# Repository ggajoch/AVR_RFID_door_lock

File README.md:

# AVR_RFID_door_lock
Door lock and opener using AVR microcontroller and RFID card

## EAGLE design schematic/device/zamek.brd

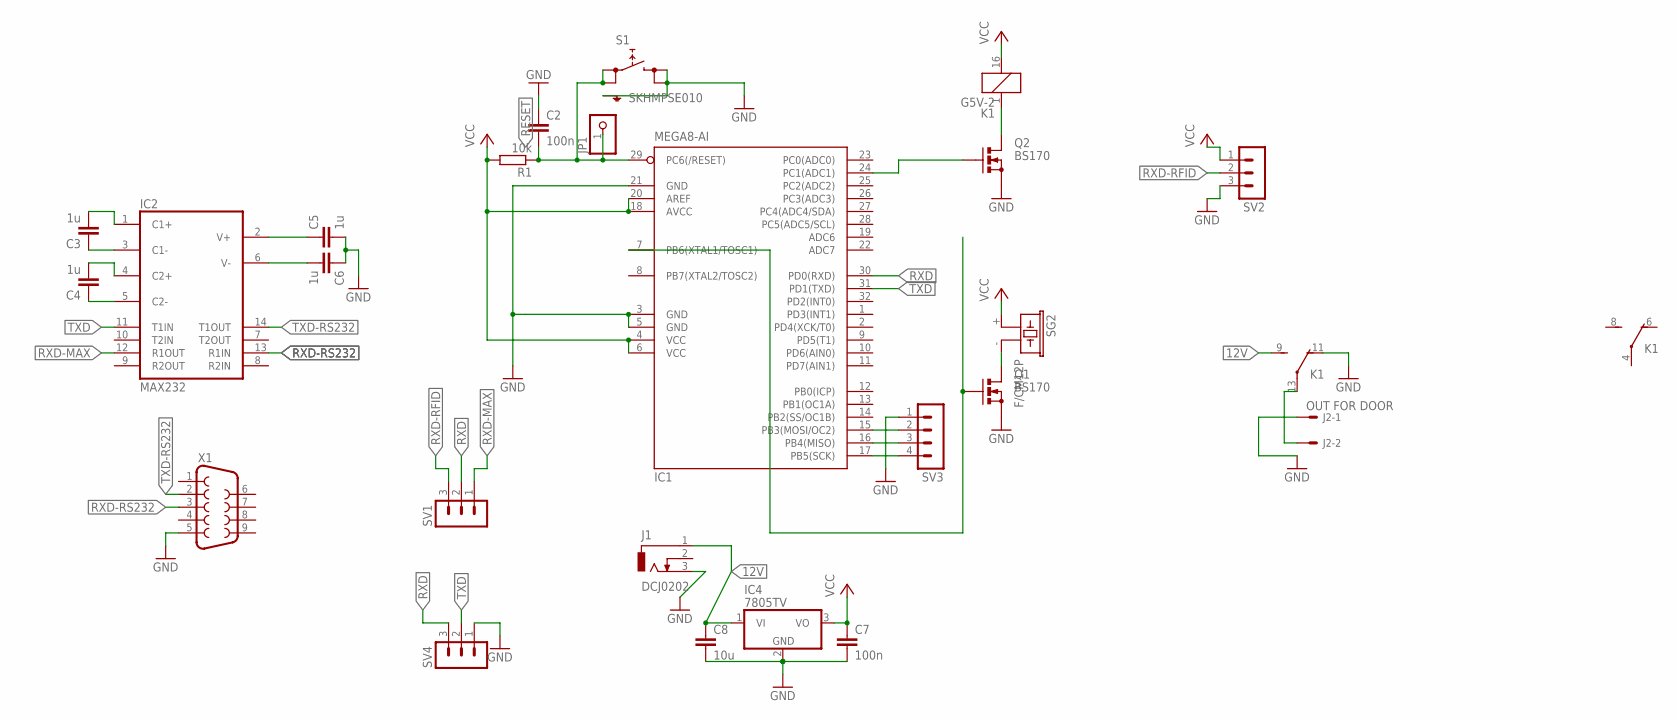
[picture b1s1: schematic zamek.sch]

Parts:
C2, C7: 100n; C1206
C3, C4, C5, C6: 1u; C1206
C8: 10u; C5B3
IC1: MEGA8-AI; TQFP32-08
IC2: MAX232; DIL16
IC4: 7805TV; TO220V
J1: DCJ0202
J2: OUT FOR DOOR; 6410-02
JP1: PINHD-1X1; 1X01
K1: G5V-2
Q1, Q2: BS170; SOT54E
R1: 10k; R1206
S1: SKHMPSE010; SKHMPXE010
SG2: F/CM12P
SV1, SV2, SV4: MA03-1
SV3: MA04-1
X1: F09HP

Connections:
12V: C8.1, IC4.1 (VI), J1.1, K1.9 (S)
GND: C2.1, C5.2, C6.1, C7.2, C8.2, IC1.3 (GND), IC1.5 (GND), IC1.21 (GND), IC2.15 (GND), IC4.2 (GND), J1.3, J2.1, K1.11 (O), Q1.S, Q2.S, S1.3 (2.1), S1.4 (2.2), S1.5 (SH), SV2.3, SV3.1, SV4.1, X1.5
MISO: IC1.16 (PB4(MISO)), SV3.3
MOSI: IC1.15 (PB3(MOSI/OC2)), SV3.2
unnamed: C5.1, IC2.2 (V+)
unnamed: C6.2, IC2.6 (V-)
unnamed: C3.1, IC2.3 (C1-)
unnamed: C4.1, IC2.5 (C2-)
unnamed: C4.2, IC2.4 (C2+)
unnamed: C3.2, IC2.1 (C1+)
unnamed: Q1.D, SG2.- (2)
unnamed: IC1.24 (PC1(ADC1)), Q2.G
unnamed: K1.1, Q2.D
unnamed: IC1.7 (PB6(XTAL1/TOSC1)), Q1.G
unnamed: J2.2, K1.13
RESET: C2.2, IC1.29 (PC6(/RESET)), JP1.1, R1.1, S1.1 (1.1), S1.2 (1.2)
RXD: IC1.30 (PD0(RXD)), SV1.2, SV4.3
RXD-MAX: IC2.12 (R1OUT), SV1.1
RXD-RFID: SV1.3, SV2.2
RXD-RS232: IC2.13 (R1IN), X1.3
SCK: IC1.17 (PB5(SCK)), SV3.4
TXD: IC1.31 (PD1(TXD)), IC2.11 (T1IN), SV4.2
TXD-RS232: IC2.14 (T1OUT), X1.2
VCC: C7.1, IC1.4 (VCC), IC1.6 (VCC), IC1.18 (AVCC), IC1.20 (AREF), IC2.16 (VCC), IC4.3 (VO), K1.16 (2), R1.2, SG2.+ (1), SV2.1

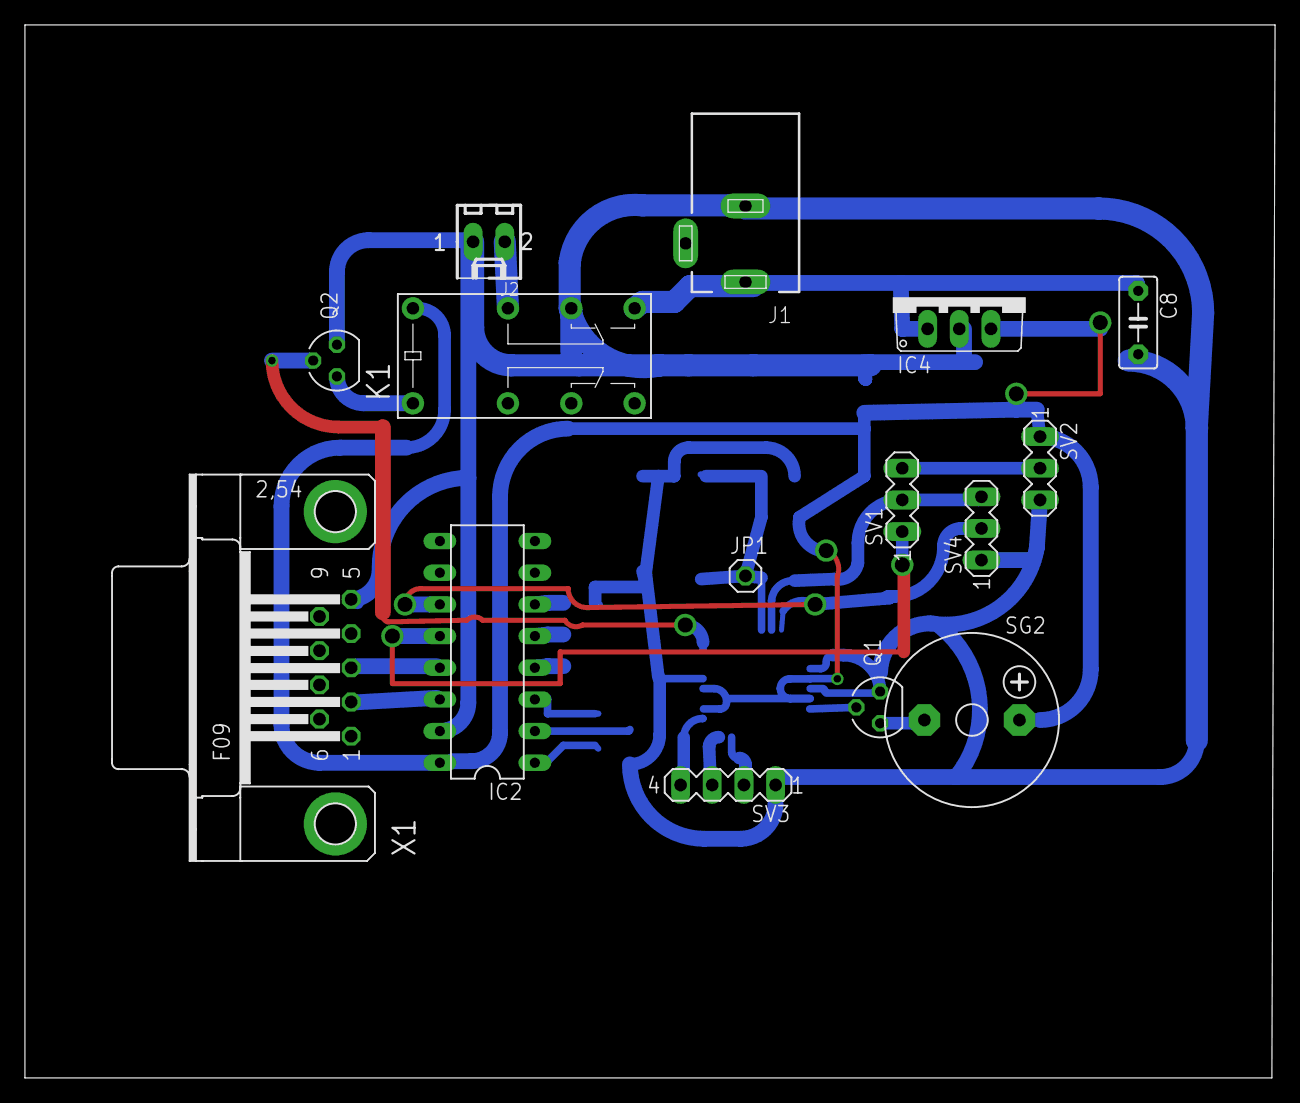
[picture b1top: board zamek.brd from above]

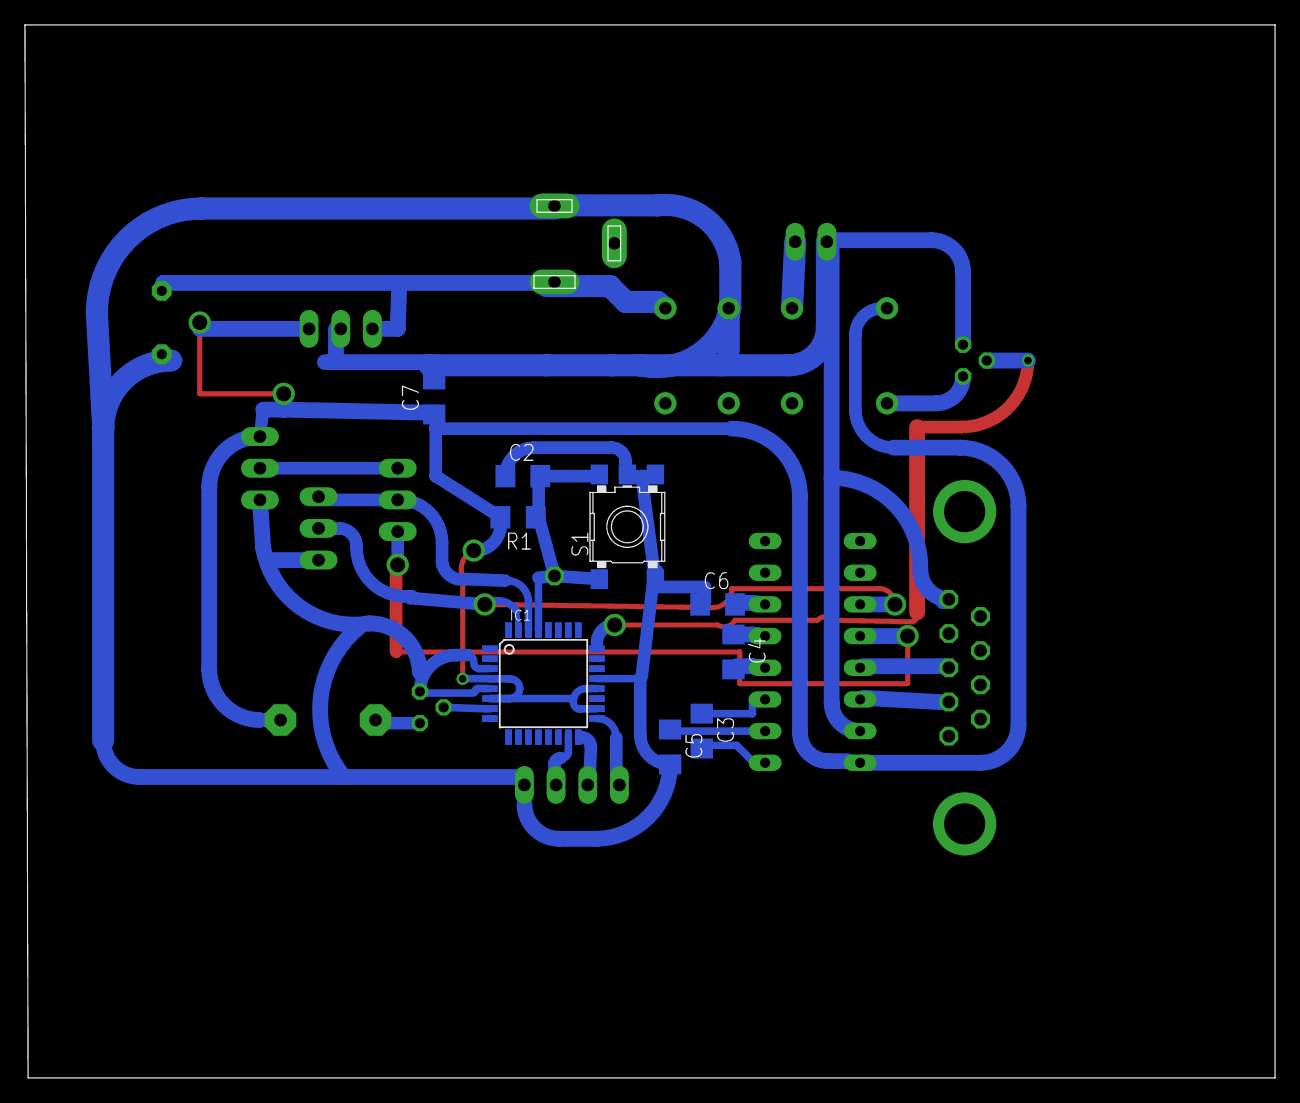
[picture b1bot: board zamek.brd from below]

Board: 2 copper layers, 100.3 x 84.4 mm, 24 parts (9 on the bottom side), 24 nets.

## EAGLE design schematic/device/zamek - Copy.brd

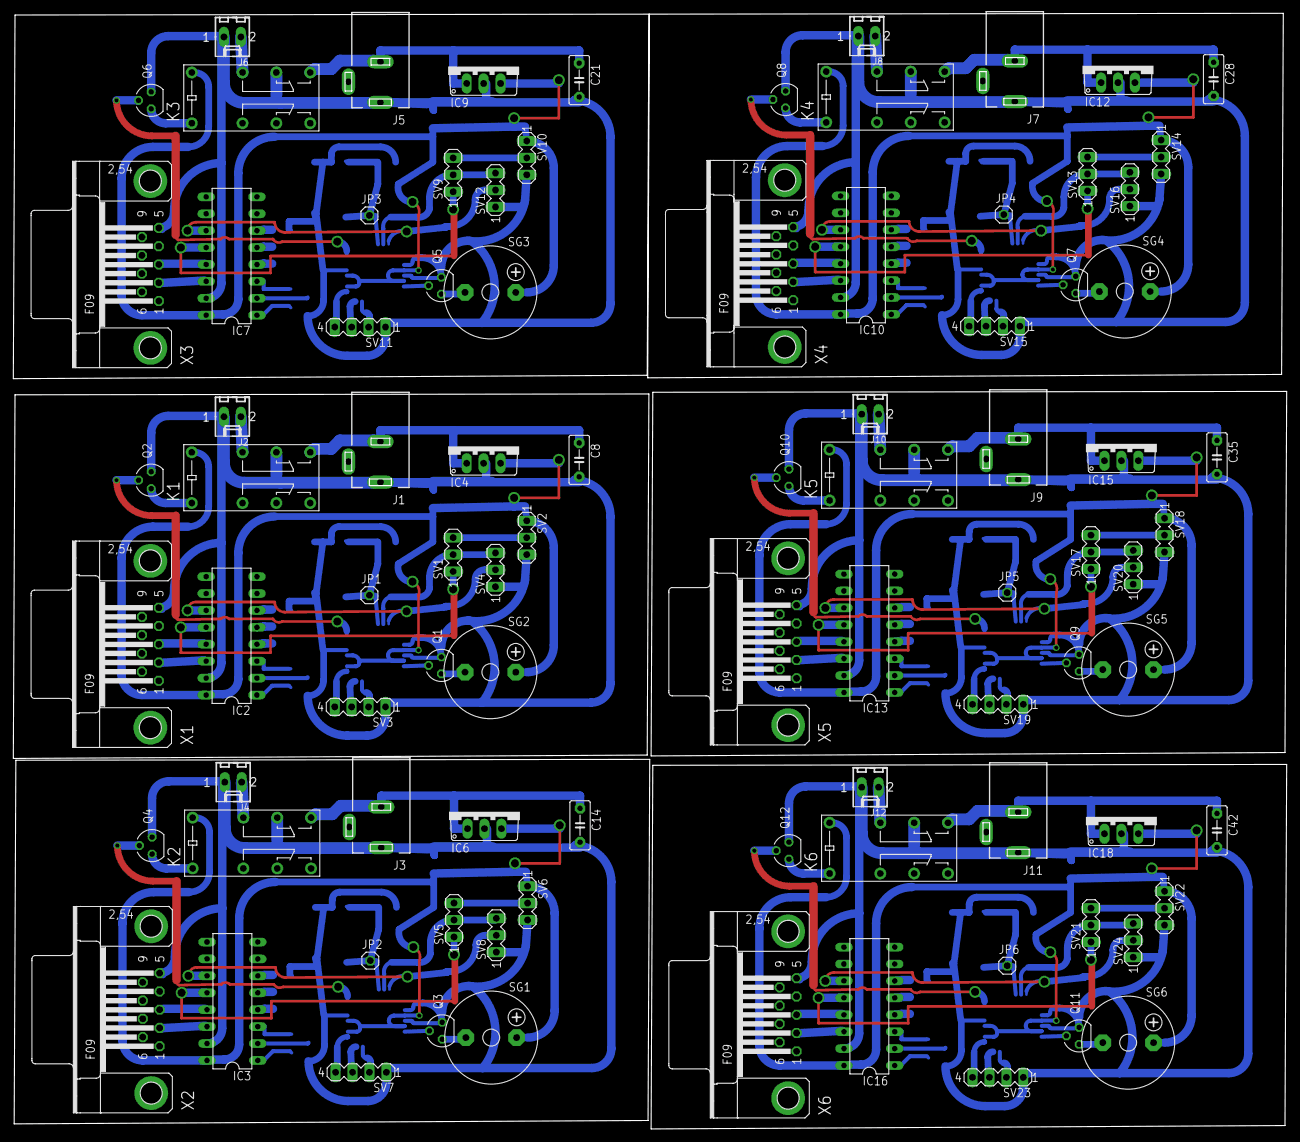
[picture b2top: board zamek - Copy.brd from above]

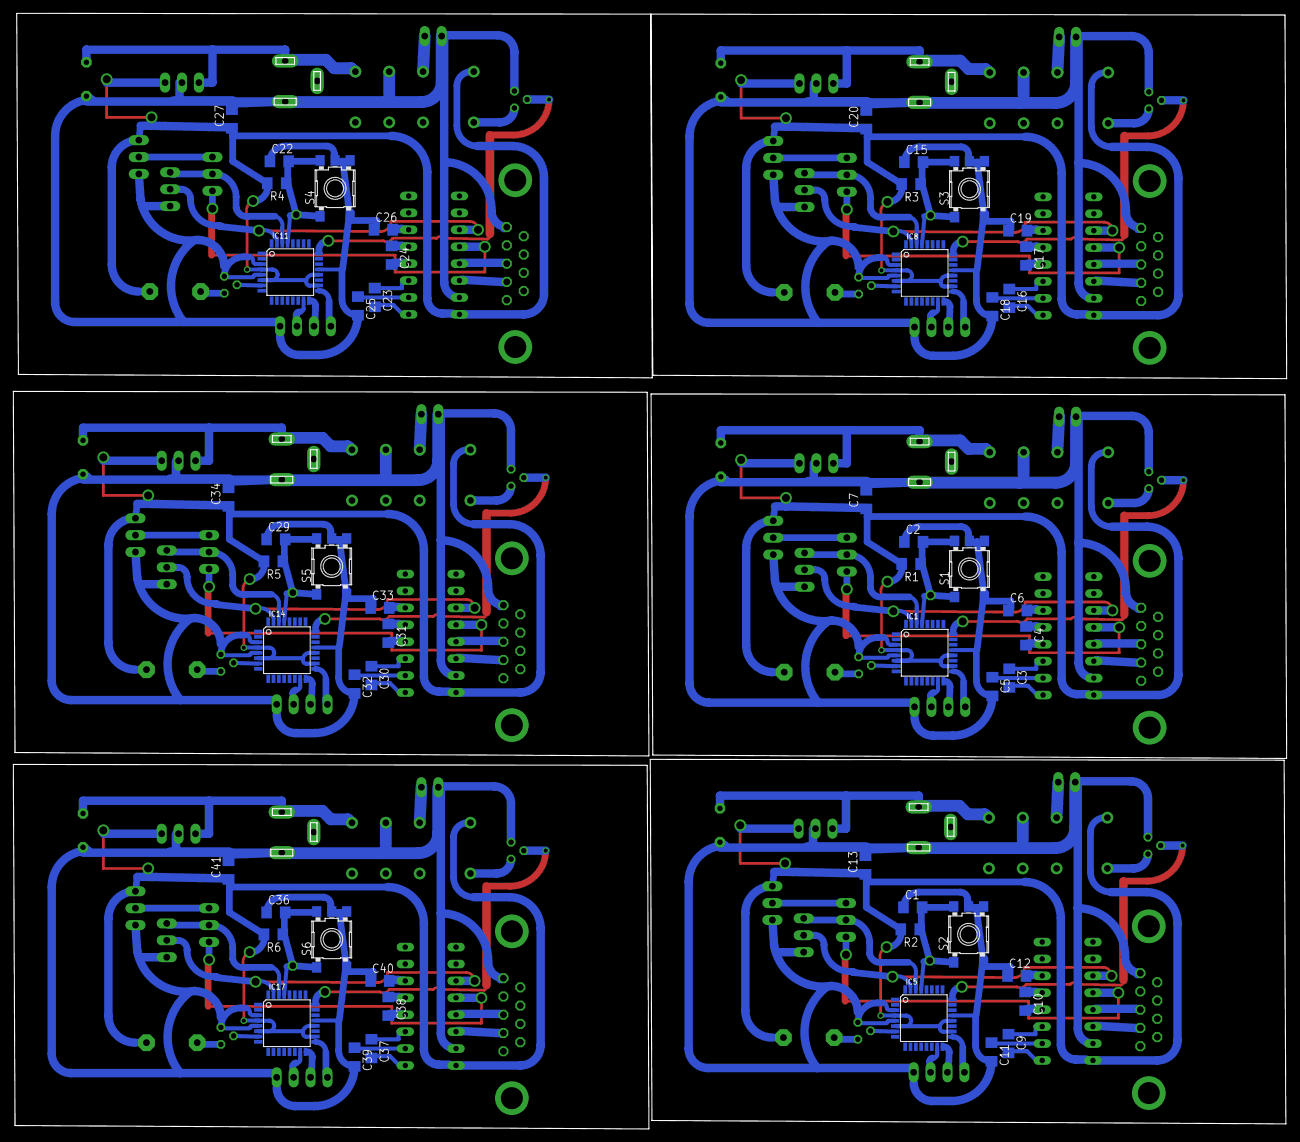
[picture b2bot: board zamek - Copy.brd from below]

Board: 2 copper layers, 191.2 x 167.5 mm, 144 parts (54 on the bottom side), 144 nets.

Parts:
C1, C2, C7, C13, C15, C20, C22, C27, C29, C34, C36, C41: 100n; C1206
C3, C4, C5, C6, C9, C10, C11, C12, C16, C17, C18, C19, C23, C24, C25, C26, C30, C31, C32, C33, C37, C38, C39, C40: 1u; C1206
C8, C14, C21, C28, C35, C42: 10u; C5B3
IC1, IC5, IC8, IC11, IC14, IC17: MEGA8-AI; TQFP32-08
IC2, IC3, IC7, IC10, IC13, IC16: MAX232; DIL16
IC4, IC6, IC9, IC12, IC15, IC18: 7805TV; TO220V
J1, J3, J5, J7, J9, J11: DCJ0202
J2, J4, J6, J8, J10, J12: OUT FOR DOOR; 6410-02
JP1, JP2, JP3, JP4, JP5, JP6: 1X01
K1, K2, K3, K4, K5, K6: G5V-2
Q1, Q2, Q3, Q4, Q5, Q6, Q7, Q8, Q9, Q10, Q11, Q12: BS170; SOT54E
R1, R2, R3, R4, R5, R6: 10k; R1206
S1, S2, S3, S4, S5, S6: SKHMPSE010; SKHMPXE010
SG1, SG2, SG3, SG4, SG5, SG6: F/CM12P
SV1, SV2, SV4, SV5, SV6, SV8, SV9, SV10, SV12, SV13, SV14, SV16, SV17, SV18, SV20, SV21, SV22, SV24: MA03-1
SV3, SV7, SV11, SV15, SV19, SV23: MA04-1
X1, X2, X3, X4, X5, X6: F09HP

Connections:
12V: C8.1, IC4.1, J1.3, K1.9
12V1: C14.1, IC6.1, J3.3, K2.9
12V2: C21.1, IC9.1, J5.3, K3.9
12V3: C28.1, IC12.1, J7.3, K4.9
12V4: C35.1, IC15.1, J9.3, K5.9
12V5: C42.1, IC18.1, J11.3, K6.9
GND: C2.1, C5.2, C6.1, C7.2, C8.2, IC1.3, IC1.5, IC1.21, IC2.15, IC4.2, J1.1, J2.1, K1.11, Q1.S, Q2.S, S1.3, S1.4, S1.5, SV2.3, SV3.1, SV4.1, X1.5
GND1: C1.1, C11.2, C12.1, C13.2, C14.2, IC3.15, IC5.3, IC5.5, IC5.21, IC6.2, J3.1, J4.1, K2.11, Q3.S, Q4.S, S2.3, S2.4, S2.5, SV6.3, SV7.1, SV8.1, X2.5
GND2: C15.1, C18.2, C19.1, C20.2, C21.2, IC7.15, IC8.3, IC8.5, IC8.21, IC9.2, J5.1, J6.1, K3.11, Q5.S, Q6.S, S3.3, S3.4, S3.5, SV10.3, SV11.1, SV12.1, X3.5
GND3: C22.1, C25.2, C26.1, C27.2, C28.2, IC10.15, IC11.3, IC11.5, IC11.21, IC12.2, J7.1, J8.1, K4.11, Q7.S, Q8.S, S4.3, S4.4, S4.5, SV14.3, SV15.1, SV16.1, X4.5
GND4: C29.1, C32.2, C33.1, C34.2, C35.2, IC13.15, IC14.3, IC14.5, IC14.21, IC15.2, J9.1, J10.1, K5.11, Q9.S, Q10.S, S5.3, S5.4, S5.5, SV18.3, SV19.1, SV20.1, X5.5
GND5: C36.1, C39.2, C40.1, C41.2, C42.2, IC16.15, IC17.3, IC17.5, IC17.21, IC18.2, J11.1, J12.1, K6.11, Q11.S, Q12.S, S6.3, S6.4, S6.5, SV22.3, SV23.1, SV24.1, X6.5
MISO: IC1.16, SV3.3
MISO1: IC5.16, SV7.3
MISO2: IC8.16, SV11.3
MISO3: IC11.16, SV15.3
MISO4: IC14.16, SV19.3
MISO5: IC17.16, SV23.3
MOSI: IC1.15, SV3.2
MOSI1: IC5.15, SV7.2
MOSI2: IC8.15, SV11.2
MOSI3: IC11.15, SV15.2
MOSI4: IC14.15, SV19.2
MOSI5: IC17.15, SV23.2
unnamed: C5.1, IC2.2
unnamed: C6.2, IC2.6
unnamed: C3.1, IC2.3
unnamed: C4.1, IC2.5
unnamed: C4.2, IC2.4
unnamed: C3.2, IC2.1
unnamed: Q1.D, SG2.-
unnamed: IC1.24, Q2.G
unnamed: K1.1, Q2.D
unnamed: IC1.7, Q1.G
unnamed: J2.2, K1.13
unnamed: C11.1, IC3.2
unnamed: C12.2, IC3.6
unnamed: C9.1, IC3.3
unnamed: C10.1, IC3.5
unnamed: C10.2, IC3.4
unnamed: C9.2, IC3.1
unnamed: IC5.24, Q4.G
unnamed: IC5.7, Q3.G
unnamed: K2.1, Q4.D
unnamed: J4.2, K2.13
unnamed: Q3.D, SG1.-
unnamed: C18.1, IC7.2
unnamed: C19.2, IC7.6
unnamed: C16.1, IC7.3
unnamed: C17.1, IC7.5
unnamed: C17.2, IC7.4
unnamed: C16.2, IC7.1
unnamed: IC8.24, Q6.G
unnamed: IC8.7, Q5.G
unnamed: K3.1, Q6.D
unnamed: J6.2, K3.13
unnamed: Q5.D, SG3.-
unnamed: C25.1, IC10.2
unnamed: C26.2, IC10.6
unnamed: C23.1, IC10.3
unnamed: C24.1, IC10.5
unnamed: C24.2, IC10.4
unnamed: C23.2, IC10.1
unnamed: IC11.24, Q8.G
unnamed: IC11.7, Q7.G
unnamed: K4.1, Q8.D
unnamed: J8.2, K4.13
unnamed: Q7.D, SG4.-
unnamed: C32.1, IC13.2
unnamed: C33.2, IC13.6
unnamed: C30.1, IC13.3
unnamed: C31.1, IC13.5
unnamed: C31.2, IC13.4
unnamed: C30.2, IC13.1
unnamed: IC14.24, Q10.G
unnamed: IC14.7, Q9.G
unnamed: K5.1, Q10.D
unnamed: J10.2, K5.13
unnamed: Q9.D, SG5.-
unnamed: C39.1, IC16.2
unnamed: C40.2, IC16.6
unnamed: C37.1, IC16.3
unnamed: C38.1, IC16.5
unnamed: C38.2, IC16.4
unnamed: C37.2, IC16.1
unnamed: IC17.24, Q12.G
unnamed: IC17.7, Q11.G
unnamed: K6.1, Q12.D
unnamed: J12.2, K6.13
unnamed: Q11.D, SG6.-
RESET: C2.2, IC1.29, JP1.1, R1.1, S1.1, S1.2
RESET1: C1.2, IC5.29, JP2.1, R2.1, S2.1, S2.2
RESET2: C15.2, IC8.29, JP3.1, R3.1, S3.1, S3.2
RESET3: C22.2, IC11.29, JP4.1, R4.1, S4.1, S4.2
RESET4: C29.2, IC14.29, JP5.1, R5.1, S5.1, S5.2
RESET5: C36.2, IC17.29, JP6.1, R6.1, S6.1, S6.2
RXD: IC1.30, SV1.2, SV4.3
RXD1: IC5.30, SV5.2, SV8.3
RXD2: IC8.30, SV9.2, SV12.3
RXD3: IC11.30, SV13.2, SV16.3
RXD4: IC14.30, SV17.2, SV20.3
RXD5: IC17.30, SV21.2, SV24.3
RXD-MAX: IC2.12, SV1.1
RXD-MAX1: IC3.12, SV5.1
RXD-MAX2: IC7.12, SV9.1
RXD-MAX3: IC10.12, SV13.1
RXD-MAX4: IC13.12, SV17.1
RXD-MAX5: IC16.12, SV21.1
RXD-RFID: SV1.3, SV2.2
RXD-RFID1: SV5.3, SV6.2
RXD-RFID2: SV9.3, SV10.2
RXD-RFID3: SV13.3, SV14.2
RXD-RFID4: SV17.3, SV18.2
RXD-RFID5: SV21.3, SV22.2
RXD-RS1: IC3.13, X2.3
RXD-RS2: IC7.13, X3.3
RXD-RS3: IC10.13, X4.3
RXD-RS4: IC13.13, X5.3
RXD-RS5: IC16.13, X6.3
RXD-RS232: IC2.13, X1.3
SCK: IC1.17, SV3.4
SCK1: IC5.17, SV7.4
SCK2: IC8.17, SV11.4
SCK3: IC11.17, SV15.4
SCK4: IC14.17, SV19.4
SCK5: IC17.17, SV23.4
TXD: IC1.31, IC2.11, SV4.2
TXD1: IC3.11, IC5.31, SV8.2
TXD2: IC7.11, IC8.31, SV12.2
TXD3: IC10.11, IC11.31, SV16.2
TXD4: IC13.11, IC14.31, SV20.2
TXD5: IC16.11, IC17.31, SV24.2
TXD-RS1: IC3.14, X2.2
TXD-RS2: IC7.14, X3.2
TXD-RS3: IC10.14, X4.2
TXD-RS4: IC13.14, X5.2
TXD-RS5: IC16.14, X6.2
TXD-RS232: IC2.14, X1.2
VCC: C7.1, IC1.4, IC1.6, IC1.18, IC1.20, IC2.16, IC4.3, K1.16, R1.2, SG2.+, SV2.1
VCC1: C13.1, IC3.16, IC5.4, IC5.6, IC5.18, IC5.20, IC6.3, K2.16, R2.2, SG1.+, SV6.1
VCC2: C20.1, IC7.16, IC8.4, IC8.6, IC8.18, IC8.20, IC9.3, K3.16, R3.2, SG3.+, SV10.1
VCC3: C27.1, IC10.16, IC11.4, IC11.6, IC11.18, IC11.20, IC12.3, K4.16, R4.2, SG4.+, SV14.1
VCC4: C34.1, IC13.16, IC14.4, IC14.6, IC14.18, IC14.20, IC15.3, K5.16, R5.2, SG5.+, SV18.1
VCC5: C41.1, IC16.16, IC17.4, IC17.6, IC17.18, IC17.20, IC18.3, K6.16, R6.2, SG6.+, SV22.1

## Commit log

2015-02-04 Added firmware
2015-02-04 Board in eagle
